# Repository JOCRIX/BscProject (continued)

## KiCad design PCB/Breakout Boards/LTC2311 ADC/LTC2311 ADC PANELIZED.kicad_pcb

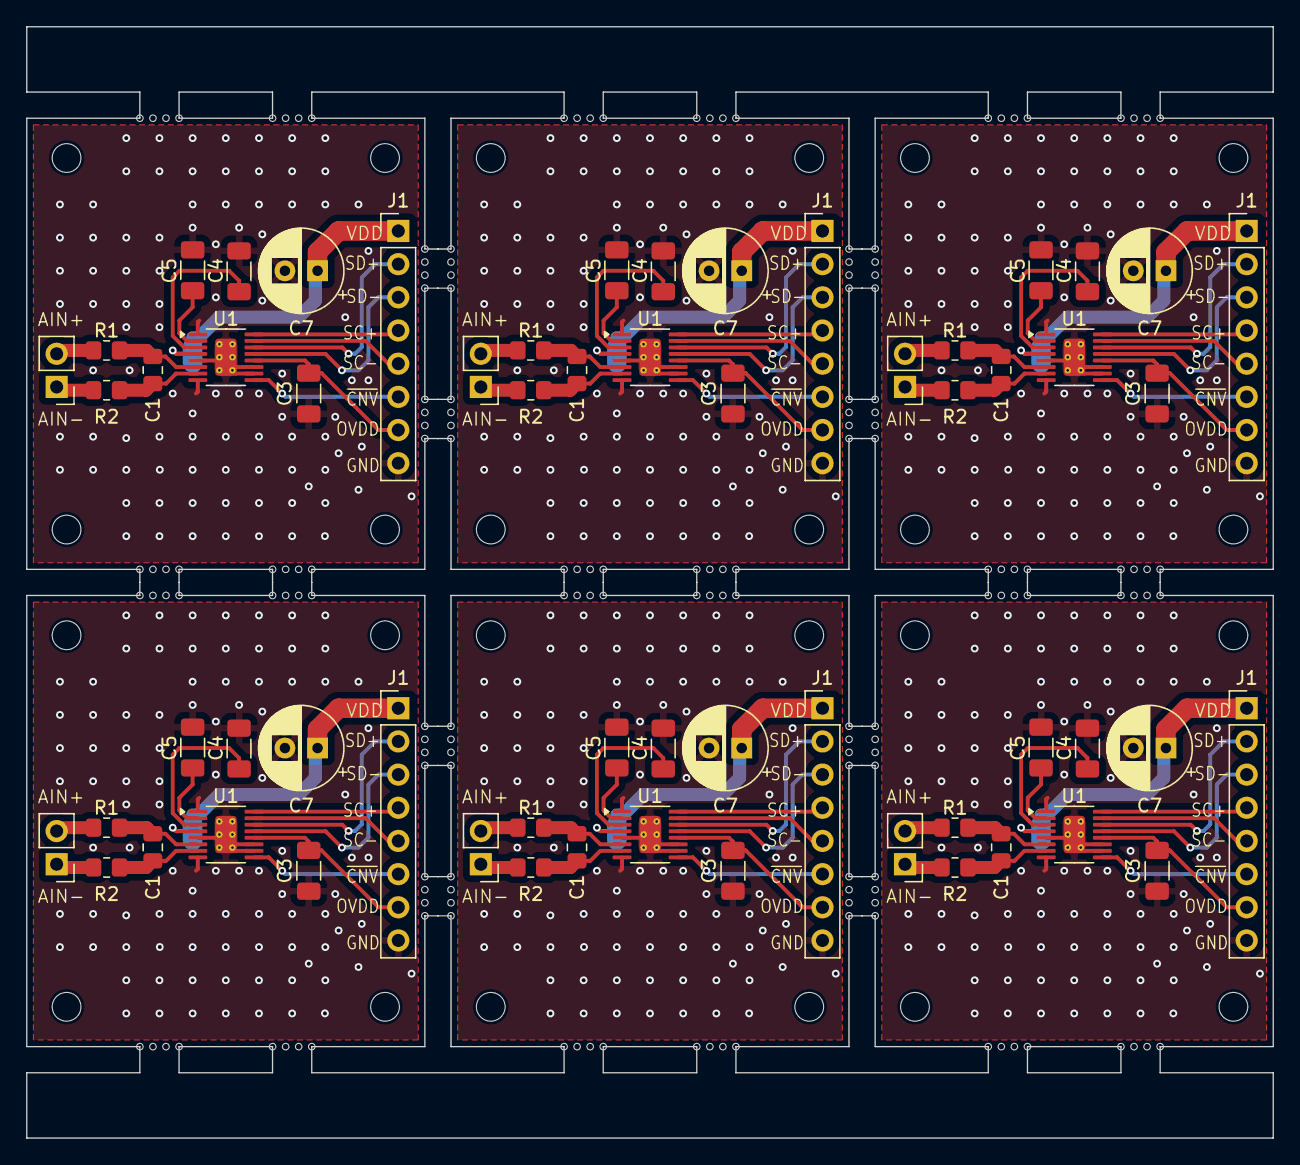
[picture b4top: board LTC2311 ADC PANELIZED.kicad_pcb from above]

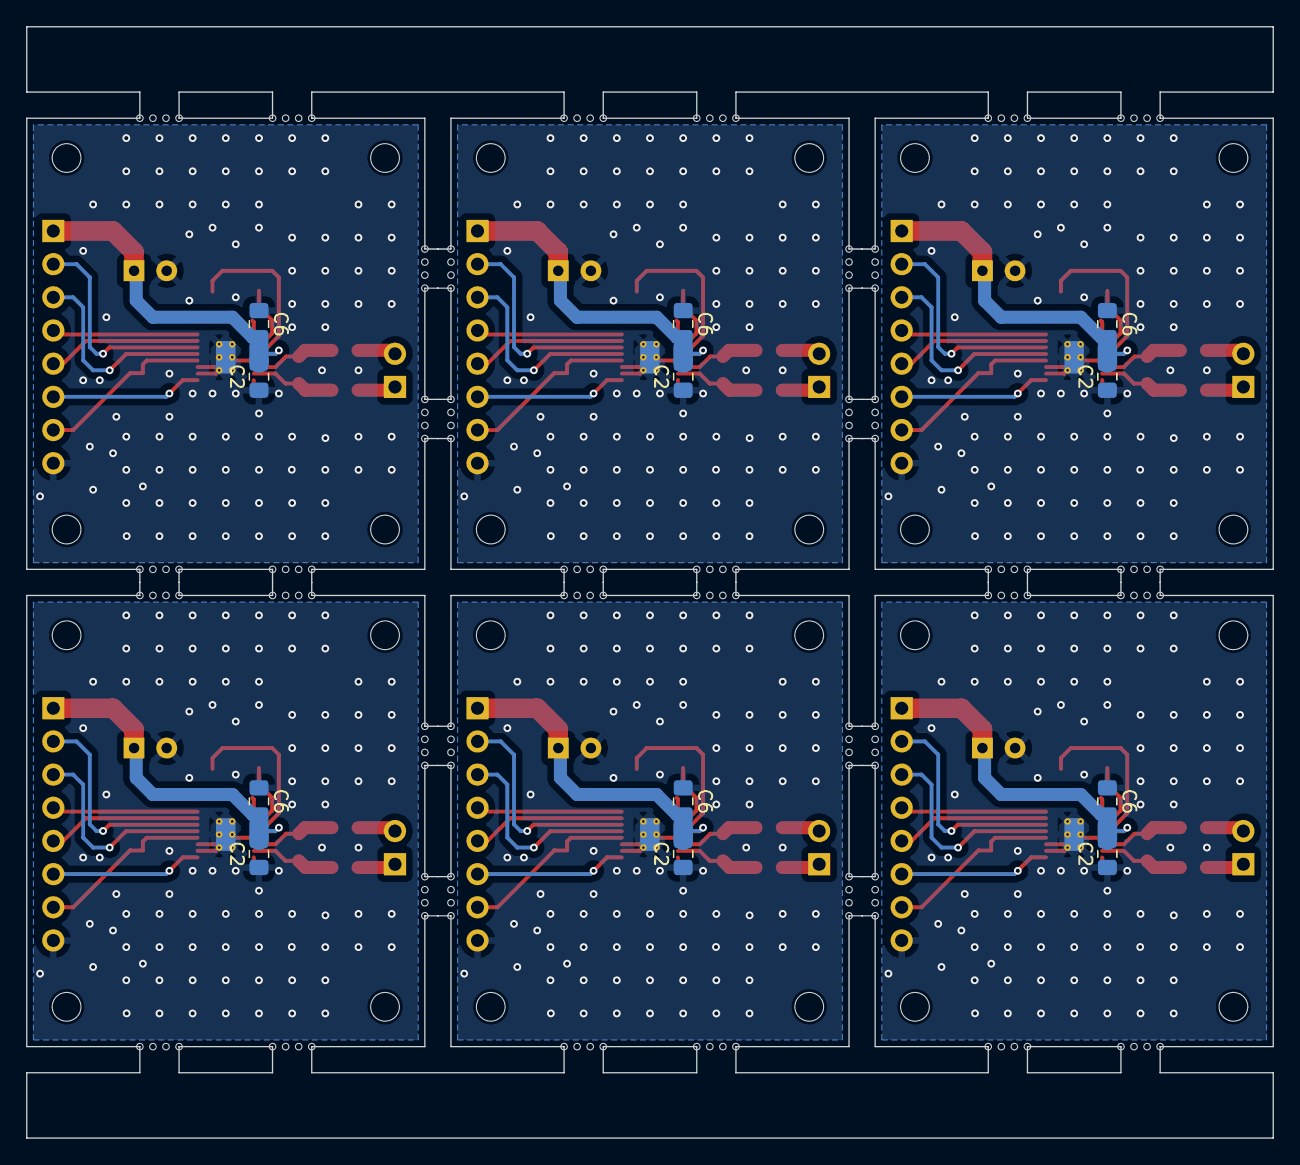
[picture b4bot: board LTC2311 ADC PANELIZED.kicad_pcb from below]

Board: 2 copper layers, 95.4 x 85.1 mm, 238 parts (12 on the bottom side), 84 nets.

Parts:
C1, C1#2, C1#3, C1#4, C1#5, C1#6: 33pF; C_0805_2012Metric_Pad1.18x1.45mm_HandSolder
C2, C2#2, C2#3, C2#4, C2#5, C2#6: 1uF; C_0805_2012Metric_Pad1.18x1.45mm_HandSolder
C3, C3#2, C3#3, C3#4, C3#5, C3#6, C4, C4#2, C4#3, C4#4, C4#5, C4#6, C5, C5#2, C5#3, C5#4, C5#5, C5#6: 10uF; C_1206_3216Metric_Pad1.33x1.80mm_HandSolder
C6, C6#2, C6#3, C6#4, C6#5, C6#6: 100nF; C_0805_2012Metric_Pad1.18x1.45mm_HandSolder
C7, C7#2, C7#3, C7#4, C7#5, C7#6: 100uF; CP_Radial_D6.3mm_P2.50mm
J1, J1#2, J1#3, J1#4, J1#5, J1#6: Conn_01x08; PinHeader_1x08_P2.54mm_Vertical
J2, J2#2, J2#3, J2#4, J2#5, J2#6: Conn_01x02; PinHeader_1x02_P2.54mm_Vertical
KiKit_MB_1_1, KiKit_MB_1_2, KiKit_MB_1_3, KiKit_MB_1_4, KiKit_MB_2_1, KiKit_MB_2_2, KiKit_MB_2_3, KiKit_MB_2_4, KiKit_MB_3_1, KiKit_MB_3_2, KiKit_MB_3_3, KiKit_MB_3_4, KiKit_MB_4_1, KiKit_MB_4_2, KiKit_MB_4_3, KiKit_MB_4_4, KiKit_MB_5_1, KiKit_MB_5_2, KiKit_MB_5_3, KiKit_MB_5_4, KiKit_MB_6_1, KiKit_MB_6_2, KiKit_MB_6_3, KiKit_MB_6_4, KiKit_MB_7_1, KiKit_MB_7_2, KiKit_MB_7_3, KiKit_MB_7_4, KiKit_MB_8_1, KiKit_MB_8_2, KiKit_MB_8_3, KiKit_MB_8_4, KiKit_MB_9_1, KiKit_MB_9_2, KiKit_MB_9_3, KiKit_MB_9_4, KiKit_MB_10_1, KiKit_MB_10_2, KiKit_MB_10_3, KiKit_MB_10_4, KiKit_MB_11_1, KiKit_MB_11_2, KiKit_MB_11_3, KiKit_MB_11_4, KiKit_MB_12_1, KiKit_MB_12_2, KiKit_MB_12_3, KiKit_MB_12_4, KiKit_MB_13_1, KiKit_MB_13_2, KiKit_MB_13_3, KiKit_MB_13_4, KiKit_MB_14_1, KiKit_MB_14_2, KiKit_MB_14_3, KiKit_MB_14_4, KiKit_MB_15_1, KiKit_MB_15_2, KiKit_MB_15_3, KiKit_MB_15_4, KiKit_MB_16_1, KiKit_MB_16_2, KiKit_MB_16_3, KiKit_MB_16_4, KiKit_MB_17_1, KiKit_MB_17_2, KiKit_MB_17_3, KiKit_MB_17_4, KiKit_MB_18_1, KiKit_MB_18_2, KiKit_MB_18_3, KiKit_MB_18_4, KiKit_MB_19_1, KiKit_MB_19_2, KiKit_MB_19_3, KiKit_MB_19_4, KiKit_MB_20_1, KiKit_MB_20_2, KiKit_MB_20_3, KiKit_MB_20_4, KiKit_MB_21_1, KiKit_MB_21_2, KiKit_MB_21_3, KiKit_MB_21_4, KiKit_MB_22_1, KiKit_MB_22_2, KiKit_MB_22_3, KiKit_MB_22_4, KiKit_MB_23_1, KiKit_MB_23_2, KiKit_MB_23_3, KiKit_MB_23_4, KiKit_MB_24_1, KiKit_MB_24_2, KiKit_MB_24_3, KiKit_MB_24_4, KiKit_MB_25_1, KiKit_MB_25_2, KiKit_MB_25_3, KiKit_MB_25_4, KiKit_MB_26_1, KiKit_MB_26_2, KiKit_MB_26_3, KiKit_MB_26_4, KiKit_MB_27_1, KiKit_MB_27_2, KiKit_MB_27_3, KiKit_MB_27_4, KiKit_MB_28_1, KiKit_MB_28_2, KiKit_MB_28_3, KiKit_MB_28_4, KiKit_MB_29_1, KiKit_MB_29_2, KiKit_MB_29_3, KiKit_MB_29_4, KiKit_MB_30_1, KiKit_MB_30_2, KiKit_MB_30_3, KiKit_MB_30_4, KiKit_MB_31_1, KiKit_MB_31_2, KiKit_MB_31_3, KiKit_MB_31_4, KiKit_MB_32_1, KiKit_MB_32_2, KiKit_MB_32_3, KiKit_MB_32_4, KiKit_MB_33_1, KiKit_MB_33_2, KiKit_MB_33_3, KiKit_MB_33_4, KiKit_MB_34_1, KiKit_MB_34_2, KiKit_MB_34_3, KiKit_MB_34_4, KiKit_MB_35_1, KiKit_MB_35_2, KiKit_MB_35_3, KiKit_MB_35_4, KiKit_MB_36_1, KiKit_MB_36_2, KiKit_MB_36_3, KiKit_MB_36_4, KiKit_MB_37_1, KiKit_MB_37_2, KiKit_MB_37_3, KiKit_MB_37_4, KiKit_MB_38_1, KiKit_MB_38_2, KiKit_MB_38_3, KiKit_MB_38_4, KiKit_MB_39_1, KiKit_MB_39_2, KiKit_MB_39_3, KiKit_MB_39_4, KiKit_MB_40_1, KiKit_MB_40_2, KiKit_MB_40_3, KiKit_MB_40_4: NPTH
M2, M2#2, M2#3, M2#4, M2#5, M2#6: MountingHole_2.2mm_M2
R1, R1#2, R1#3, R1#4, R1#5, R1#6, R2, R2#2, R2#3, R2#4, R2#5, R2#6: 24R9; R_0805_2012Metric_Pad1.20x1.40mm_HandSolder
U1, U1#2, U1#3, U1#4, U1#5, U1#6: LTC2311; MSOP-16-1EP_3x4mm_P0.5mm_EP1.65x2.85mm_ThermalVias

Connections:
Board_0-GND: C2#2.1, C3#3.1, C4.1, C5.1, C6#6.1, C7.2, J1#5.8, U1.1 (GND), U1.5 (GND), U1.8 (GND), U1.10 (~CMOS/LVDS), U1.11 (GND), U1.17 (GND)
Board_0-Net-(J1-Pin_1): C2#2.2, C6#6.2, C7.1, J1#5.1, U1.4 (VDD)
Board_0-Net-(J1-Pin_2): J1#5.2, U1.14 (SDO+)
Board_0-Net-(J1-Pin_3): J1#5.3, U1.13 (SDO-)
Board_0-Net-(J1-Pin_4): J1#5.4, U1.16 (SCK+)
Board_0-Net-(J1-Pin_5): J1#5.5, U1.15 (SCK-)
Board_0-Net-(J1-Pin_6): J1#5.6, U1.9 (~CNV)
Board_0-Net-(J1-Pin_7): C3#3.2, J1#5.7, U1.12 (OVDD)
Board_0-Net-(J2-Pin_1): J2#4.1, R2#5.1
Board_0-Net-(J2-Pin_2): J2#4.2, R1#4.1
Board_0-Net-(U1-AIN+): C1.1, R1#4.2, U1.6 (AIN+)
Board_0-Net-(U1-AIN-): C1.2, R2#5.2, U1.7 (AIN-)
Board_0-Net-(U1-REFIN): C5.2, U1.2 (REFIN)
Board_0-Net-(U1-REFOUT): C4.2, U1.3 (REFOUT)
Board_1-GND: C2.1, C3#5.1, C4#2.1, C5#5.1, C6#2.1, C7#3.2, J1#6.8, U1#2.1 (GND), U1#2.5 (GND), U1#2.8 (GND), U1#2.10 (~CMOS/LVDS), U1#2.11 (GND), U1#2.17 (GND)
Board_1-Net-(J1-Pin_1): C2.2, C6#2.2, C7#3.1, J1#6.1, U1#2.4 (VDD)
Board_1-Net-(J1-Pin_2): J1#6.2, U1#2.14 (SDO+)
Board_1-Net-(J1-Pin_3): J1#6.3, U1#2.13 (SDO-)
Board_1-Net-(J1-Pin_4): J1#6.4, U1#2.16 (SCK+)
Board_1-Net-(J1-Pin_5): J1#6.5, U1#2.15 (SCK-)
Board_1-Net-(J1-Pin_6): J1#6.6, U1#2.9 (~CNV)
Board_1-Net-(J1-Pin_7): C3#5.2, J1#6.7, U1#2.12 (OVDD)
Board_1-Net-(J2-Pin_1): J2#3.1, R2#4.1
Board_1-Net-(J2-Pin_2): J2#3.2, R1#5.1
Board_1-Net-(U1-AIN+): C1#4.1, R1#5.2, U1#2.6 (AIN+)
Board_1-Net-(U1-AIN-): C1#4.2, R2#4.2, U1#2.7 (AIN-)
Board_1-Net-(U1-REFIN): C5#5.2, U1#2.2 (REFIN)
Board_1-Net-(U1-REFOUT): C4#2.2, U1#2.3 (REFOUT)
Board_2-GND: C2#4.1, C3.1, C4#5.1, C5#2.1, C6#5.1, C7#2.2, J1.8, U1#4.1 (GND), U1#4.5 (GND), U1#4.8 (GND), U1#4.10 (~CMOS/LVDS), U1#4.11 (GND), U1#4.17 (GND)
Board_2-Net-(J1-Pin_1): C2#4.2, C6#5.2, C7#2.1, J1.1, U1#4.4 (VDD)
Board_2-Net-(J1-Pin_2): J1.2, U1#4.14 (SDO+)
Board_2-Net-(J1-Pin_3): J1.3, U1#4.13 (SDO-)
Board_2-Net-(J1-Pin_4): J1.4, U1#4.16 (SCK+)
Board_2-Net-(J1-Pin_5): J1.5, U1#4.15 (SCK-)
Board_2-Net-(J1-Pin_6): J1.6, U1#4.9 (~CNV)
Board_2-Net-(J1-Pin_7): C3.2, J1.7, U1#4.12 (OVDD)
Board_2-Net-(J2-Pin_1): J2#6.1, R2#3.1
Board_2-Net-(J2-Pin_2): J2#6.2, R1#3.1
Board_2-Net-(U1-AIN+): C1#6.1, R1#3.2, U1#4.6 (AIN+)
Board_2-Net-(U1-AIN-): C1#6.2, R2#3.2, U1#4.7 (AIN-)
Board_2-Net-(U1-REFIN): C5#2.2, U1#4.2 (REFIN)
Board_2-Net-(U1-REFOUT): C4#5.2, U1#4.3 (REFOUT)
Board_3-GND: C2#3.1, C3#6.1, C4#4.1, C5#4.1, C6#4.1, C7#6.2, J1#4.8, U1#3.1 (GND), U1#3.5 (GND), U1#3.8 (GND), U1#3.10 (~CMOS/LVDS), U1#3.11 (GND), U1#3.17 (GND)
Board_3-Net-(J1-Pin_1): C2#3.2, C6#4.2, C7#6.1, J1#4.1, U1#3.4 (VDD)
Board_3-Net-(J1-Pin_2): J1#4.2, U1#3.14 (SDO+)
Board_3-Net-(J1-Pin_3): J1#4.3, U1#3.13 (SDO-)
Board_3-Net-(J1-Pin_4): J1#4.4, U1#3.16 (SCK+)
Board_3-Net-(J1-Pin_5): J1#4.5, U1#3.15 (SCK-)
Board_3-Net-(J1-Pin_6): J1#4.6, U1#3.9 (~CNV)
Board_3-Net-(J1-Pin_7): C3#6.2, J1#4.7, U1#3.12 (OVDD)
Board_3-Net-(J2-Pin_1): J2.1, R2#2.1
Board_3-Net-(J2-Pin_2): J2.2, R1#6.1
Board_3-Net-(U1-AIN+): C1#3.1, R1#6.2, U1#3.6 (AIN+)
Board_3-Net-(U1-AIN-): C1#3.2, R2#2.2, U1#3.7 (AIN-)
Board_3-Net-(U1-REFIN): C5#4.2, U1#3.2 (REFIN)
Board_3-Net-(U1-REFOUT): C4#4.2, U1#3.3 (REFOUT)
Board_4-GND: C2#6.1, C3#2.1, C4#3.1, C5#6.1, C6#3.1, C7#4.2, J1#3.8, U1#6.1 (GND), U1#6.5 (GND), U1#6.8 (GND), U1#6.10 (~CMOS/LVDS), U1#6.11 (GND), U1#6.17 (GND)
Board_4-Net-(J1-Pin_1): C2#6.2, C6#3.2, C7#4.1, J1#3.1, U1#6.4 (VDD)
Board_4-Net-(J1-Pin_2): J1#3.2, U1#6.14 (SDO+)
Board_4-Net-(J1-Pin_3): J1#3.3, U1#6.13 (SDO-)
Board_4-Net-(J1-Pin_4): J1#3.4, U1#6.16 (SCK+)
Board_4-Net-(J1-Pin_5): J1#3.5, U1#6.15 (SCK-)
Board_4-Net-(J1-Pin_6): J1#3.6, U1#6.9 (~CNV)
Board_4-Net-(J1-Pin_7): C3#2.2, J1#3.7, U1#6.12 (OVDD)
Board_4-Net-(J2-Pin_1): J2#5.1, R2#6.1
Board_4-Net-(J2-Pin_2): J2#5.2, R1.1
Board_4-Net-(U1-AIN+): C1#5.1, R1.2, U1#6.6 (AIN+)
Board_4-Net-(U1-AIN-): C1#5.2, R2#6.2, U1#6.7 (AIN-)
Board_4-Net-(U1-REFIN): C5#6.2, U1#6.2 (REFIN)
Board_4-Net-(U1-REFOUT): C4#3.2, U1#6.3 (REFOUT)
Board_5-GND: C2#5.1, C3#4.1, C4#6.1, C5#3.1, C6.1, C7#5.2, J1#2.8, U1#5.1 (GND), U1#5.5 (GND), U1#5.8 (GND), U1#5.10 (~CMOS/LVDS), U1#5.11 (GND), U1#5.17 (GND)
Board_5-Net-(J1-Pin_1): C2#5.2, C6.2, C7#5.1, J1#2.1, U1#5.4 (VDD)
Board_5-Net-(J1-Pin_2): J1#2.2, U1#5.14 (SDO+)
Board_5-Net-(J1-Pin_3): J1#2.3, U1#5.13 (SDO-)
Board_5-Net-(J1-Pin_4): J1#2.4, U1#5.16 (SCK+)
Board_5-Net-(J1-Pin_5): J1#2.5, U1#5.15 (SCK-)
Board_5-Net-(J1-Pin_6): J1#2.6, U1#5.9 (~CNV)
Board_5-Net-(J1-Pin_7): C3#4.2, J1#2.7, U1#5.12 (OVDD)
Board_5-Net-(J2-Pin_1): J2#2.1, R2.1
Board_5-Net-(J2-Pin_2): J2#2.2, R1#2.1
Board_5-Net-(U1-AIN+): C1#2.1, R1#2.2, U1#5.6 (AIN+)
Board_5-Net-(U1-AIN-): C1#2.2, R2.2, U1#5.7 (AIN-)
Board_5-Net-(U1-REFIN): C5#3.2, U1#5.2 (REFIN)
Board_5-Net-(U1-REFOUT): C4#6.2, U1#5.3 (REFOUT)

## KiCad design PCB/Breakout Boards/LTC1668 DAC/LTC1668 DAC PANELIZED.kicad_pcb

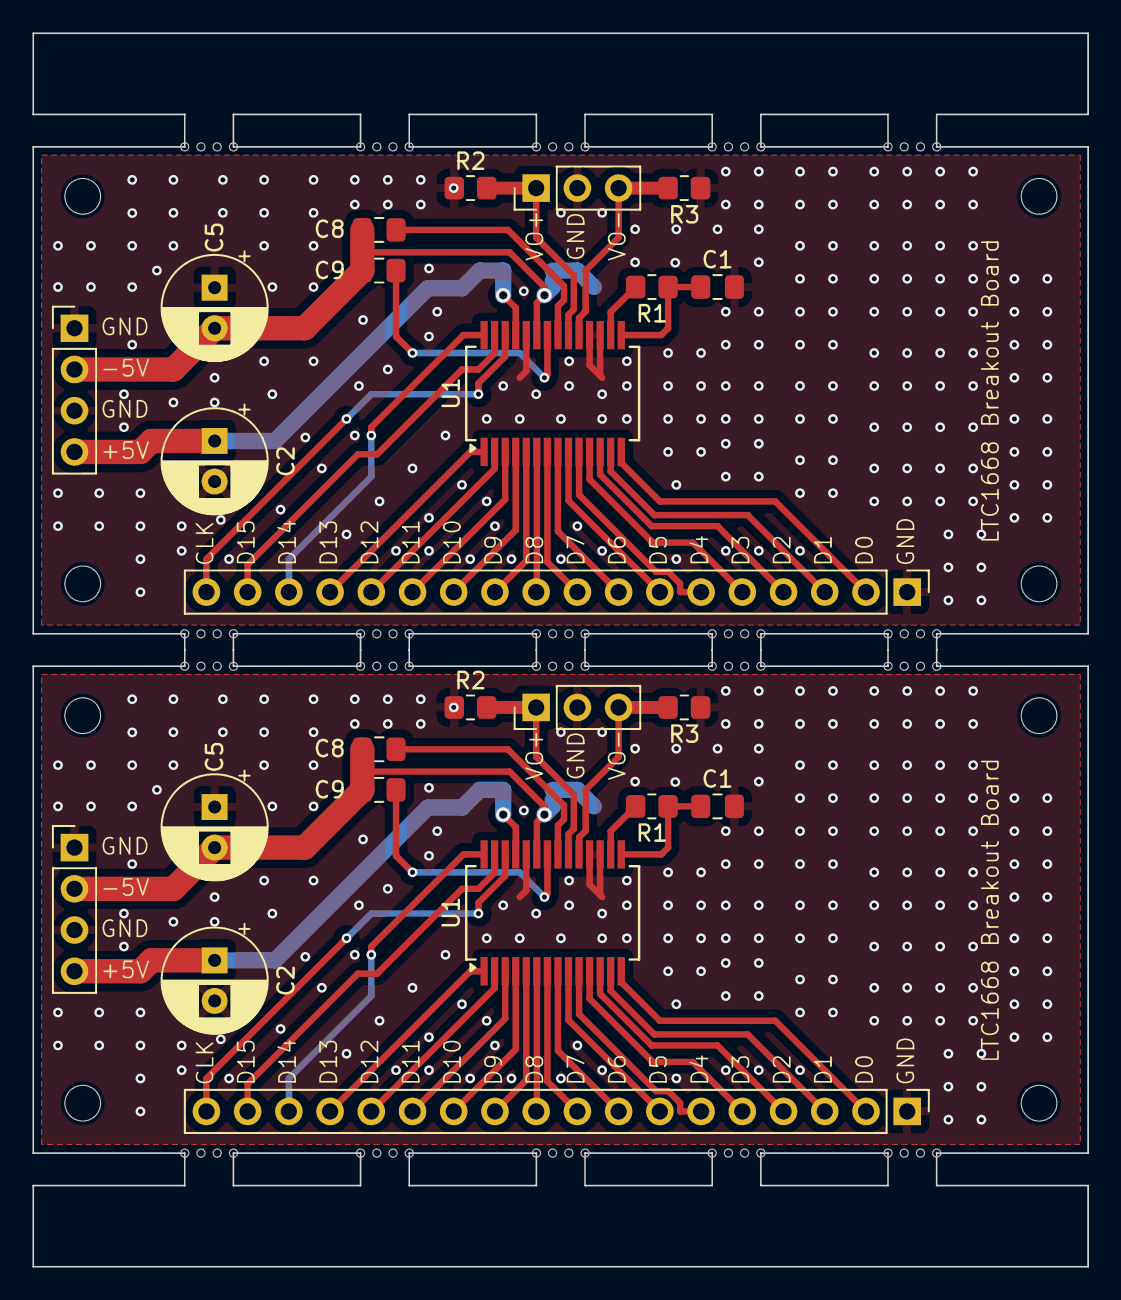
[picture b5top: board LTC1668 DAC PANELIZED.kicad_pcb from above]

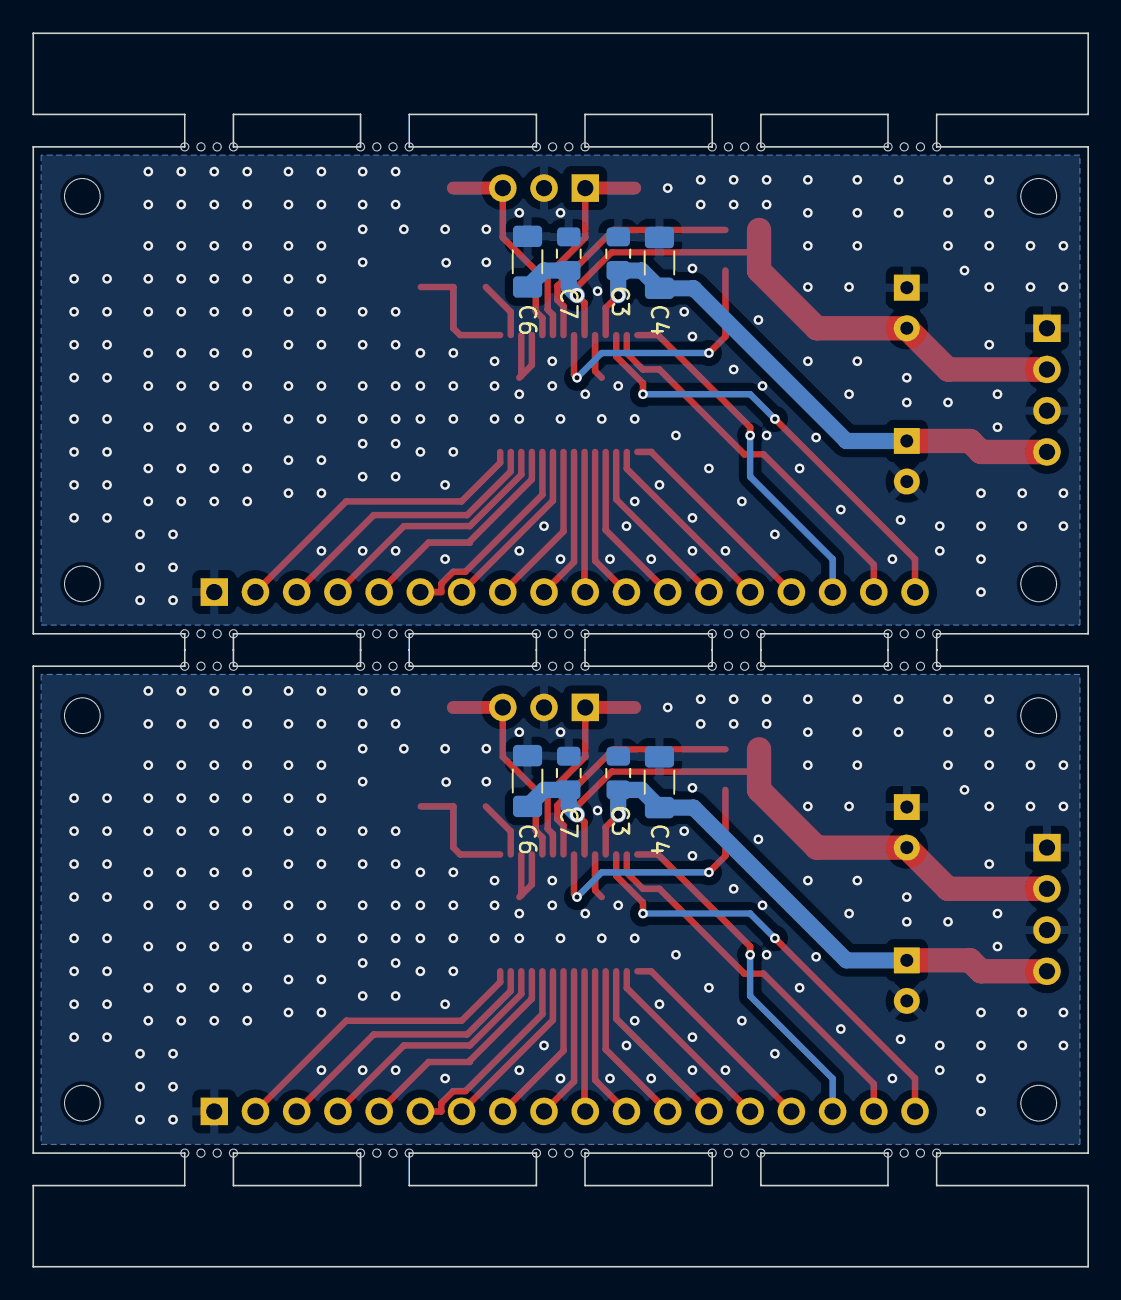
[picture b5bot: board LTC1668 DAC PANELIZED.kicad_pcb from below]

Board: 2 copper layers, 65.0 x 76.0 mm, 112 parts (8 on the bottom side), 52 nets.

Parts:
C1, C1#2, C3, C3#2, C7, C7#2, C8, C8#2, C9, C9#2: 100nF; C_0805_2012Metric_Pad1.18x1.45mm_HandSolder
C2, C2#2, C5, C5#2: 100uF; CP_Radial_D6.3mm_P2.50mm
C4, C4#2, C6, C6#2: 10uF; C_1206_3216Metric_Pad1.33x1.80mm_HandSolder
J2, J2#2: Conn_01x18; PinHeader_1x18_P2.54mm_Vertical
J3, J3#2: Conn_01x03; PinHeader_1x03_P2.54mm_Vertical
J4, J4#2: Conn_01x04; PinHeader_1x04_P2.54mm_Vertical
KiKit_MB_1_1, KiKit_MB_1_2, KiKit_MB_1_3, KiKit_MB_1_4, KiKit_MB_2_1, KiKit_MB_2_2, KiKit_MB_2_3, KiKit_MB_2_4, KiKit_MB_3_1, KiKit_MB_3_2, KiKit_MB_3_3, KiKit_MB_3_4, KiKit_MB_4_1, KiKit_MB_4_2, KiKit_MB_4_3, KiKit_MB_4_4, KiKit_MB_5_1, KiKit_MB_5_2, KiKit_MB_5_3, KiKit_MB_5_4, KiKit_MB_6_1, KiKit_MB_6_2, KiKit_MB_6_3, KiKit_MB_6_4, KiKit_MB_7_1, KiKit_MB_7_2, KiKit_MB_7_3, KiKit_MB_7_4, KiKit_MB_8_1, KiKit_MB_8_2, KiKit_MB_8_3, KiKit_MB_8_4, KiKit_MB_9_1, KiKit_MB_9_2, KiKit_MB_9_3, KiKit_MB_9_4, KiKit_MB_10_1, KiKit_MB_10_2, KiKit_MB_10_3, KiKit_MB_10_4, KiKit_MB_11_1, KiKit_MB_11_2, KiKit_MB_11_3, KiKit_MB_11_4, KiKit_MB_12_1, KiKit_MB_12_2, KiKit_MB_12_3, KiKit_MB_12_4, KiKit_MB_13_1, KiKit_MB_13_2, KiKit_MB_13_3, KiKit_MB_13_4, KiKit_MB_14_1, KiKit_MB_14_2, KiKit_MB_14_3, KiKit_MB_14_4, KiKit_MB_15_1, KiKit_MB_15_2, KiKit_MB_15_3, KiKit_MB_15_4, KiKit_MB_16_1, KiKit_MB_16_2, KiKit_MB_16_3, KiKit_MB_16_4, KiKit_MB_17_1, KiKit_MB_17_2, KiKit_MB_17_3, KiKit_MB_17_4, KiKit_MB_18_1, KiKit_MB_18_2, KiKit_MB_18_3, KiKit_MB_18_4, KiKit_MB_19_1, KiKit_MB_19_2, KiKit_MB_19_3, KiKit_MB_19_4, KiKit_MB_20_1, KiKit_MB_20_2, KiKit_MB_20_3, KiKit_MB_20_4: NPTH
R1, R1#2: 2k; R_0805_2012Metric_Pad1.20x1.40mm_HandSolder
R2, R2#2, R3, R3#2: 52R3; R_0805_2012Metric_Pad1.20x1.40mm_HandSolder
U1, U1#2: LTC1668CG; SSOP-28_5.3x10.2mm_P0.65mm

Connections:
Board_0-/+5V: C2#2.1, C3#2.1, C4.1, J4#2.4, U1.25 (VDD)
Board_0-/-5V: C5#2.2, C6#2.1, C7.1, C8.1, C9.1, J4#2.2, U1.23 (VSS)
Board_0-/VOUT+: J3#2.1, R2.2, U1.20 (IOUT_A)
Board_0-/VOUT-: J3#2.3, R3#2.2, U1.19 (IOUT_B)
Board_0-GND: C1.2, C2#2.2, C3#2.2, C4.2, C5#2.1, C6#2.2, C7.2, J2.1, J3#2.2, J4#2.1, J4#2.3, R2.1, R3#2.1, U1.17 (AGND), U1.18 (LADCOM), U1.24 (DGND)
Board_0-Net-(J2-Pin_2): J2.2, U1.14 (DB0(LSB))
Board_0-Net-(J2-Pin_3): J2.3, U1.13 (DB1)
Board_0-Net-(J2-Pin_4): J2.4, U1.12 (DB2)
Board_0-Net-(J2-Pin_5): J2.5, U1.11 (DB3)
Board_0-Net-(J2-Pin_6): J2.6, U1.10 (DB4)
Board_0-Net-(J2-Pin_7): J2.7, U1.9 (DB5)
Board_0-Net-(J2-Pin_8): J2.8, U1.8 (DB6)
Board_0-Net-(J2-Pin_9): J2.9, U1.7 (DB7)
Board_0-Net-(J2-Pin_10): J2.10, U1.6 (DB8)
Board_0-Net-(J2-Pin_11): J2.11, U1.5 (DB9)
Board_0-Net-(J2-Pin_12): J2.12, U1.4 (DB10)
Board_0-Net-(J2-Pin_13): J2.13, U1.3 (DB11)
Board_0-Net-(J2-Pin_14): J2.14, U1.2 (DB12)
Board_0-Net-(J2-Pin_15): J2.15, U1.1 (DB13)
Board_0-Net-(J2-Pin_16): J2.16, U1.28 (DB14)
Board_0-Net-(J2-Pin_17): J2.17, U1.27 (DB15(MSB))
Board_0-Net-(J2-Pin_18): J2.18, U1.26 (CLK)
Board_0-Net-(U1-COMP1): C8.2, U1.21 (COMP1)
Board_0-Net-(U1-COMP2): C9.2, U1.22 (COMP2)
Board_0-Net-(U1-IREFIN): R1#2.2, U1.16 (IREFIN)
Board_0-Net-(U1-REFOUT): C1.1, R1#2.1, U1.15 (REFOUT)
Board_1-/+5V: C2.1, C3.1, C4#2.1, J4.4, U1#2.25 (VDD)
Board_1-/-5V: C5.2, C6.1, C7#2.1, C8#2.1, C9#2.1, J4.2, U1#2.23 (VSS)
Board_1-/VOUT+: J3.1, R2#2.2, U1#2.20 (IOUT_A)
Board_1-/VOUT-: J3.3, R3.2, U1#2.19 (IOUT_B)
Board_1-GND: C1#2.2, C2.2, C3.2, C4#2.2, C5.1, C6.2, C7#2.2, J2#2.1, J3.2, J4.1, J4.3, R2#2.1, R3.1, U1#2.17 (AGND), U1#2.18 (LADCOM), U1#2.24 (DGND)
Board_1-Net-(J2-Pin_2): J2#2.2, U1#2.14 (DB0(LSB))
Board_1-Net-(J2-Pin_3): J2#2.3, U1#2.13 (DB1)
Board_1-Net-(J2-Pin_4): J2#2.4, U1#2.12 (DB2)
Board_1-Net-(J2-Pin_5): J2#2.5, U1#2.11 (DB3)
Board_1-Net-(J2-Pin_6): J2#2.6, U1#2.10 (DB4)
Board_1-Net-(J2-Pin_7): J2#2.7, U1#2.9 (DB5)
Board_1-Net-(J2-Pin_8): J2#2.8, U1#2.8 (DB6)
Board_1-Net-(J2-Pin_9): J2#2.9, U1#2.7 (DB7)
Board_1-Net-(J2-Pin_10): J2#2.10, U1#2.6 (DB8)
Board_1-Net-(J2-Pin_11): J2#2.11, U1#2.5 (DB9)
Board_1-Net-(J2-Pin_12): J2#2.12, U1#2.4 (DB10)
Board_1-Net-(J2-Pin_13): J2#2.13, U1#2.3 (DB11)
Board_1-Net-(J2-Pin_14): J2#2.14, U1#2.2 (DB12)
Board_1-Net-(J2-Pin_15): J2#2.15, U1#2.1 (DB13)
Board_1-Net-(J2-Pin_16): J2#2.16, U1#2.28 (DB14)
Board_1-Net-(J2-Pin_17): J2#2.17, U1#2.27 (DB15(MSB))
Board_1-Net-(J2-Pin_18): J2#2.18, U1#2.26 (CLK)
Board_1-Net-(U1-COMP1): C8#2.2, U1#2.21 (COMP1)
Board_1-Net-(U1-COMP2): C9#2.2, U1#2.22 (COMP2)
Board_1-Net-(U1-IREFIN): R1.2, U1#2.16 (IREFIN)
Board_1-Net-(U1-REFOUT): C1#2.1, R1.1, U1#2.15 (REFOUT)

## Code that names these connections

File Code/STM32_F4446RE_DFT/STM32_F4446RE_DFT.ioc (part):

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Mcu.Name=STM32F446R(C-E)Tx
Mcu.Package=LQFP64
Mcu.UserName=STM32F446RETx
PA0-WKUP.GPIOParameters=GPIO_Label
PA0-WKUP.GPIO_Label=DB_RESET
PA0-WKUP.Signal=GPIO_Output
PA1.GPIOParameters=GPIO_Label
PA1.GPIO_Label=V_PGA_A0
PA1.Signal=GPIO_Output
PA10.GPIOParameters=GPIO_Label
PA10.GPIO_Label=DAC_RANGE_A1
PA10.Signal=GPIO_Output
PA11.GPIOParameters=GPIO_Label
PA11.GPIO_Label=DAC_RANGE_EN
PA11.Signal=GPIO_Output
PA13.GPIOParameters=GPIO_Label
PA13.GPIO_Label=TMS
PA13.Mode=Serial_Wire
PA13.Signal=SYS_JTMS-SWDIO
PA14.GPIOParameters=GPIO_Label
PA14.GPIO_Label=TCK
PA14.Mode=Serial_Wire
PA14.Signal=SYS_JTCK-SWCLK
PA2.GPIOParameters=GPIO_Label
PA2.GPIO_Label=USART_TX
PA2.Mode=Asynchronous
PA2.Signal=USART2_TX
PA3.GPIOParameters=GPIO_Label
PA3.GPIO_Label=USART_RX
PA3.Mode=Asynchronous
PA3.Signal=USART2_RX
PA4.GPIOParameters=GPIO_Label
PA4.GPIO_Label=RANGE_SER_DATA
PA4.Signal=GPIO_Output
PA5.GPIOParameters=GPIO_Label
PA5.GPIO_Label=LD2 [Green Led]
PA5.Signal=GPIO_Output
PA6.GPIOParameters=GPIO_Label
PA6.GPIO_Label=RANGE_SER_CLK
PA6.Signal=GPIO_Output
PA7.GPIOParameters=GPIO_Label
PA7.GPIO_Label=RANGE_SER_LATCH
PA7.Signal=GPIO_Output
PA8.GPIOParameters=GPIO_Label
PA8.GPIO_Label=Test_Input
PA8.Signal=GPIO_Input
PA9.GPIOParameters=GPIO_Label
PA9.GPIO_Label=DAC_RANGE_A0
PA9.Signal=GPIO_Output
PB0.GPIOParameters=GPIO_Speed,PinState,GPIO_Label
PB0.GPIO_Label=DB0
PB0.GPIO_Speed=GPIO_SPEED_FREQ_VERY_HIGH
PB0.PinState=GPIO_PIN_RESET
PB0.Signal=GPIO_Output
PB1.GPIOParameters=GPIO_Label
PB1.GPIO_Label=DB1
PB1.Signal=GPIO_Output
PB10.GPIOParameters=GPIO_Label
PB10.GPIO_Label=V_PGA_A1
PB10.Signal=GPIO_Output
PB12.GPIOParameters=GPIO_Label
PB12.GPIO_Label=V_PGA_A2
PB12.Signal=GPIO_Output
PB13.GPIOParameters=GPIO_Label
PB13.GPIO_Label=I_PGA_A0
PB13.Signal=GPIO_Output
PB14.GPIOParameters=GPIO_Label
PB14.GPIO_Label=I_PGA_A1
PB14.Signal=GPIO_Output
PB15.GPIOParameters=GPIO_Label
PB15.GPIO_Label=I_PGA_A2
PB15.Signal=GPIO_Output
PB2.GPIOParameters=GPIO_Label
PB2.GPIO_Label=DB2
PB2.Signal=GPIO_Output
PB3.GPIOParameters=GPIO_Label
PB3.GPIO_Label=DB3
PB3.Signal=GPIO_Output
PB4.GPIOParameters=GPIO_Label
PB4.GPIO_Label=DB4
PB4.Signal=GPIO_Output
PB5.GPIOParameters=GPIO_Label
PB5.GPIO_Label=DB5
PB5.Signal=GPIO_Output
PB6.GPIOParameters=GPIO_Label
PB6.GPIO_Label=DB6
PB6.Signal=GPIO_Output
PB7.GPIOParameters=GPIO_Label
PB7.GPIO_Label=DB7
PB7.Signal=GPIO_Output
PB9.GPIOParameters=GPIO_Label
PB9.GPIO_Label=DB_RW
PB9.Signal=GPIO_Output
PC0.GPIOParameters=GPIO_Label
PC0.GPIO_Label=DB8
PC0.Signal=GPIO_Output
PC1.GPIOParameters=GPIO_Label
PC1.GPIO_Label=DB9
PC1.Signal=GPIO_Output
PC10.GPIOParameters=GPIO_Label
PC10.GPIO_Label=TimerPin
PC10.Signal=GPIO_Output
PC12.GPIOParameters=GPIO_Label
PC12.GPIO_Label=UART5_TX_DISPLAY
PC12.Signal=UART5_TX
PC13.GPIOParameters=GPIO_Label,GPIO_ModeDefaultEXTI
PC13.GPIO_Label=B1 [Blue PushButton]
PC13.GPIO_ModeDefaultEXTI=GPIO_MODE_IT_FALLING
PC13.Signal=GPXTI13
PC14-OSC32_IN.Mode=LSE-External-Oscillator
PC14-OSC32_IN.Signal=RCC_OSC32_IN
PC15-OSC32_OUT.Mode=LSE-External-Oscillator
PC15-OSC32_OUT.Signal=RCC_OSC32_OUT
PC2.GPIOParameters=GPIO_Label
PC2.GPIO_Label=DB10
PC2.Signal=GPIO_Output
PC3.GPIOParameters=GPIO_Label
PC3.GPIO_Label=DB11
PC3.Signal=GPIO_Output
PC4.GPIOParameters=GPIO_Label
PC4.GPIO_Label=DB12
PC4.Signal=GPIO_Output
PC5.GPIOParameters=GPIO_Label
PC5.GPIO_Label=DB13
PC5.Signal=GPIO_Output
PC6.GPIOParameters=GPIO_Label
PC6.GPIO_Label=DB14
PC6.Signal=GPXTI6
PC7.GPIOParameters=GPIO_Label
PC7.GPIO_Label=DB15
PC7.Signal=GPIO_Output
PC8.GPIOParameters=GPIO_Label
PC8.GPIO_Label=DB_IX
PC8.Signal=GPIO_Output
PC9.GPIOParameters=GPIO_Label
PC9.GPIO_Label=DB_CLK
PC9.Signal=GPIO_Output
PD2.GPIOParameters=GPIO_Label
PD2.GPIO_Label=UART5_RX_DISPLAY
PD2.Signal=UART5_RX
PH0-OSC_IN.Mode=HSE-External-Oscillator
PH0-OSC_IN.Signal=RCC_OSC_IN
PH1-OSC_OUT.Mode=HSE-External-Oscillator
PH1-OSC_OUT.Signal=RCC_OSC_OUT
RCC.HSE_VALUE=8000000
RCC.SYSCLKFreq_VALUE=180000000
RCC.SYSCLKSource=RCC_SYSCLKSOURCE_PLLCLK
board=NUCLEO-F446RE
boardIOC=true

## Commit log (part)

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2024-09-05 Work in progress on U1733C specs
2024-09-05 stuff
2024-09-06 erge Test commit
2024-09-06 Work on COmmercialLCRMEters added U1733C data
2024-09-06 added administativ til rapport
2024-09-06 Done with CommercialLCR Meters
2024-09-06 merged 2.4 and 2.5 to one section
2024-09-06 removed as from 2.1
2024-09-06 Rename 2.2
2024-09-06 Fix ref
2024-09-06 2.3 work not done
2024-09-06 2.4 is done
2024-09-06 Done with 2_3, ready for merge
2024-09-06 Updated 2.3 section and file names and references
2024-09-07 Made document for report structure in Adminsistrative\. A suggestion for structure has been added.
2024-09-07 Fixed cite refs in 2.2
2024-09-07 Swapped 3 and 4
2024-09-09 Update .gitignore for STM32 trash files
2024-09-09 STM32 SPI Test code init
2024-09-10 added section to problem statement conclusion
2024-09-10 added comments to techAnal
2024-09-11 2.5 done
2024-09-11 Problem statement done
2024-09-11 Intro til techanal
2024-09-12 prep for 4_1 branch
2024-09-12 Branch for 4_1 work
2024-09-12 added section 4_2TypicalMeasPrin
2024-09-12 4.1 wip
2024-09-12 Progress on 4.2
2024-09-12 added pictures to 4.2
2024-09-13 4_2_whatstoneBridge done
2024-09-13 4_1 added capacitive and inductive reactans phasors missing real res
2024-09-14 DFT test
2024-09-16 test
2024-09-16 minor changes to 4.2
2024-09-16 quick command for SI called SIQ and newline called nl added
2024-09-16 2.3 WIP
2024-09-16 Merged main into 4.1 branch
2024-09-16 Table in 2.3 done
2024-09-17 4_1_Impedance analysis done
2024-09-17 New subsec 4_1_1 added
2024-09-17 4_1_1 work
2024-09-17 minor edits to ch 2 and 4
2024-09-17 changed pdf name to match title
2024-09-17 started section 4.2.1 on IV method
2024-09-18 added quick command for ref
2024-09-18 work
2024-09-18 4.1.1 wip must add library to main
2024-09-18 Added mathscr package and \Laplace newcommand
2024-09-18 added LapTran ans a command
2024-09-18 4.1.1 work
2024-09-18 done with 4_2_2
2024-09-18 Derived L/C formula, working on ESR, D,Q
2024-09-19 4.1 done
2024-09-19 added section 4_2_3
2024-09-19 Merged 4.1.1 and main
2024-09-19 Fixed error in 4.1
2024-09-19 Prep for 4_1_5 branch
2024-09-19 Small changes to vector calculations
2024-09-19 4_1_5 series to parallel done
2024-09-19 F446RE working SPI code
2024-09-20 statestick exam 1
2024-09-23 updates to exam 1 in statistics
2024-09-24 CRime
2024-09-24 more crime
2024-09-24 Done with statistics exam1
2024-09-24 timing lib dev
2024-09-25 added chapter 5
2024-09-25 Added table of requirements
2024-09-26 notes from meeting
2024-09-26 added explanation to specs
2024-09-26 ADC stuff
2024-09-26 Added modulus and argument spec
2024-09-26 teset
2024-09-27 Sys spec intro
2024-09-27 minor fix in 5.
2024-09-30 code
2024-10-01 exam 2 probability JFT
2024-10-01 minor changes to kursus structure
2024-10-01 Block diagram
2024-10-02 added system block design
2024-10-02 minor changes as per meeting
2024-10-02 minor changes
2024-10-02 added System Architecture
2024-10-02 rettelser
2024-10-02 fixed 7
2024-10-02 added changes to 2.0 and 2.1
2024-10-02 Fixed 12
2024-10-02 changes to 2.2
2024-10-02 figure of portB schematic F446RE
2024-10-03 Beskrivelse af sys arch.
2024-10-03 Sys modul section
2024-10-03 rettelser til 2.2
2024-10-03 retter end til End is arkitektur figur
2024-10-03 new system achitecture
2024-10-03 VHDL stuff
2024-10-03 Working NCO code for PIC
2024-10-04 added linear regression 1 for JFT
2024-10-04 Sec sections and subsections prepared for system architecture and modularization
2024-10-04 Sys design add
2024-10-04 Figures for each module added
2024-10-04 Upd 6_1
2024-10-04 Done with descriptions
2024-10-04 krav til front end
2024-10-04 Minor fix
2024-10-04 added requirements to all modules
2024-10-04 changed UI spec placement
2024-10-04 added interface
2024-10-06 minor changes to system interface
2024-10-07 added diagrams for memory
2024-10-07 Ram code
2024-10-07 Memory code work
2024-10-08 WIP VHDL port code
2024-10-09 Ram and PORT code
2024-10-09 Branch for port code
2024-10-09 Working RAM and port code
2024-10-11 working 2clk memory
2024-10-11 added pin map of MCU and FPGA
2024-10-12 Working, real life tester, port + memory code. Extremely important to set Pulldowns on unused data pins during testing!!
2024-10-12 Reset logic added for memory state machine
2024-10-13 MCU port code WIP
2024-10-14 .tex files for 7.1, 7.2
2024-10-14 small updates to requiremts
2024-10-14 7.2.1 wip
2024-10-14 unfukd
2024-10-14 added 6.4.3, 6.3.3 and wwrote appendix A
2024-10-14 Stuff for 7_
2024-10-15 7.2 WIP
2024-10-15 added the DAC vivado project
2024-10-15 Done med RAM blok
2024-10-15 ADC and DAC choice
2024-10-15 wip ext mem
2024-10-15 block diagram of DAC control
2024-10-16 external memory work
2024-10-16 DAC Control explained
2024-10-16 Ext mem code fixed
2024-10-16 more for DAC Control in documentation
2024-10-17 upd. ignore file
2024-10-17 ned master file
2024-10-17 pulse gen wip
2024-10-17 added DAC elements to Sample control master file
2024-10-17 added mem files to Sample control Master
2024-10-18 møde noter fra 16-10
2024-10-18 minor changes to FPGA DAC pinMap
2024-10-18 block diagram of internal logic
2024-10-18 Shit code wip for pulse gen
2024-10-19 Working pulse gen
2024-10-20 fixed figure 7.4
2024-10-21 minor changes to FPGA block diagram
2024-10-21 rettelser fra troels
2024-10-21 ExtMemDistWork
2024-10-21 Added project IV saver
2024-10-21 rettelser i rapport og diagrammer
2024-10-22 updated diagram for sample control
2024-10-22 Memory distribution v1
2024-10-22 adc work
2024-10-23 ctrl master
2024-10-23 system test file
2024-10-24 testet IV_SAVER, MEM_DIST og MEM_RW og EXT_MEM, it works
2024-10-24 working entities
2024-10-24 Update Pulse Gen
2024-10-24 Minor fix in pulse gen
2024-10-24 Working on adc control
2024-10-26 Done with Sample memory (read write), memory distribution and pulse generator
2024-10-28 modul 4 lek 1 opgaver
2024-10-28 minor changes to test of extMem
2024-10-28 ADC control work
2024-10-28 upd ignore
2024-10-28 figure of internal FPGA interface
2024-10-28 added polarity control to PulseGenV2
2024-10-28 new figures for FPGA interface added
2024-10-29 new interface figures for FPGA
2024-10-29 Fixed SPI CLK
2024-10-30 minor change to clk frw.mw
2024-10-30 ADCCOntrol test
2024-10-30 VQFN breakout board
2024-10-30 VQFN16
2024-10-30 minor changes to stm32 mem
2024-10-31 changes to stm32 commPort
2024-11-01 updated commPortCode
2024-11-01 wokring version of internal mem and commPort from STM32
2024-11-01 Working Working code for comPort for STM32
2024-11-01 Made improved pulse generator 'pulse_gen_width_modulator_invert.vhd' for ADC Control
2024-11-01 Added new version of pulse generator with pulse width modulation. Tests OK
2024-11-04 new stuff
2024-11-04 Working ADCControl Code
2024-11-04 testbench test added
2024-11-04 added pics for ADC control doc
2024-11-04 Double checked code to work with both ADCs also added comments in TOPlayer for easier routing later
2024-11-05 Working on 7_2_8 ADC Control
2024-11-06 test of memory
2024-11-06 commport
2024-11-07 Working on ADC control section
2024-11-07 commPortCode
2024-11-08 Done with ADC Control doc. Need to add some pictures to various appendixes
2024-11-08 New EMEMRW
2024-11-08 updated pulse gen appendix
2024-11-09 new version of ext mem rw
2024-11-10 rapport stuff
2024-11-10 Updated ADCControl, has better CNV stability
2024-11-10 Jitter på CNV
2024-11-10 commPort Code and FPGA EXT mem code
2024-11-11 upd rapport
2024-11-11 added logic reset function to ADC control
2024-11-11 nco stuff
2024-11-12 Working CommCode with ext mem
2024-11-12 work on adc resampler
2024-11-12 work on resampler
2024-11-13 minor comm changes
2024-11-13 resample work
2024-11-14 Added high speed ADC Control appendix
2024-11-14 resampler work
2024-11-15 functional Internal/External mem and IVSA
2024-11-15 working EXT MEM, INT MEM, IVSA and DAC
2024-11-15 adc resampler work
2024-11-15 FPGA test code
2024-11-15 Sample parallel to series converter
2024-11-16 AD Resampler done
2024-11-16 100% working FPGA
2024-11-18 resample section
2024-11-18 resmapler work
2024-11-18 Figures of IVSA and IXMUX
2024-11-18 resampler rapport work
2024-11-19 vejledernoter
2024-11-19 new figures for FPGA
2024-11-20 IVSA and IXMUX added to rapport
2024-11-20 PSC block in rapport
2024-11-21 EXT_MEM_RW update
2024-11-21 sample control intro
2024-11-22 Working shit
2024-11-25 filter work
2024-11-25 DAC LP filter passive
2024-11-26 Anti aliasing filter a-ok
2024-11-28 DAC_FILTER
2024-11-29 DAC minor changes
2024-11-29 almost there
2024-12-03 schematic v1
2024-12-03 ready for pcb
2024-12-04 corrected kicad
2024-12-05 docu doneski
2024-12-05 pcb 90%
2024-12-05 pcb 92%
2024-12-05 pcb update
2024-12-06 PCB done
2024-12-06 added source to IO buf
2024-12-06 HMI stuff
2024-12-09 DAC power
2024-12-10 complex
2024-12-10 minor stuff
2024-12-10 complex math code
2024-12-10 complex math
2024-12-11 DC power amp calculations
2024-12-17 STM32 SimpleSample code with PGA and range
2024-12-19 working dft code
2024-12-19 working DFT
2024-12-19 DAC power amp stability
2024-12-20 DAC_RANGE_CODE
2024-12-21 AutoRange C code
2024-12-21 AutoRange
2024-12-22 DAC Power Stability
2024-12-23 OpenCalculations
2024-12-23 Minor Open Correction
2024-12-25 Start of MCU section
2024-12-27 new chapter for impedance modelling
2024-12-27 Open Correction
2024-12-27 Front Page pic
2024-12-27 Frontpage pic
2024-12-27 Frontpage
2024-12-27 abstract done, TBD page number
2024-12-27 preface edited, minor addition otherwise OK
2024-12-27 added chapters for system verification, discussion and conclusion
2024-12-27 updated 7_3 intro
2024-12-27 removed sample control conclusion
2024-12-28 CommPort Set struct added to rapport
2024-12-28 small fixes
2024-12-28 7.3 conclusion done
2024-12-28 CommCode Done in Rapport
2024-12-28 minor updates
2024-12-29 Pics of Temp HMI
2024-12-29 MCU conclusion doneski
2024-12-30 Meas
2024-12-30 SpecPlots
2024-12-30 disc
2024-12-30 konklusion
2024-12-30 SpecVTest
2024-12-30 SystemVerification
2024-12-31 PCB Rapport
2025-01-01 OpenShort Pic
2025-01-02 Correction 2.0
2025-01-03 møde noter
2025-01-03 minor code changes
2025-01-03 new PCB section
2025-01-03 final corrections in the rapport
2025-01-04 fixd stuff
2025-01-04 Requirements fixed
2025-01-04 Corrections to das rapportos
2025-01-05 mcu done
2025-01-05 Almost done
2025-01-05 fixd
2025-01-05 Final stull
2025-01-05 captions fixed
2025-01-05 done
2025-01-11 statistics exam prep 1
2025-01-12 workshop 2 fremlægning
2025-01-13 New Correction
2025-01-13 statistic presentation 3
2025-01-13 Final corrections
2025-01-14 workshop 4
2025-01-15 auto range extended
2025-01-15 minor PGA auto range changes, not done
2025-01-16 opdateret fremlægning
2025-01-16 New autorange
2025-01-16 test af hmi tx
2025-01-17 minor things
2025-01-17 display 1.1
2025-01-18 display upgrades
2025-01-19 presentation
